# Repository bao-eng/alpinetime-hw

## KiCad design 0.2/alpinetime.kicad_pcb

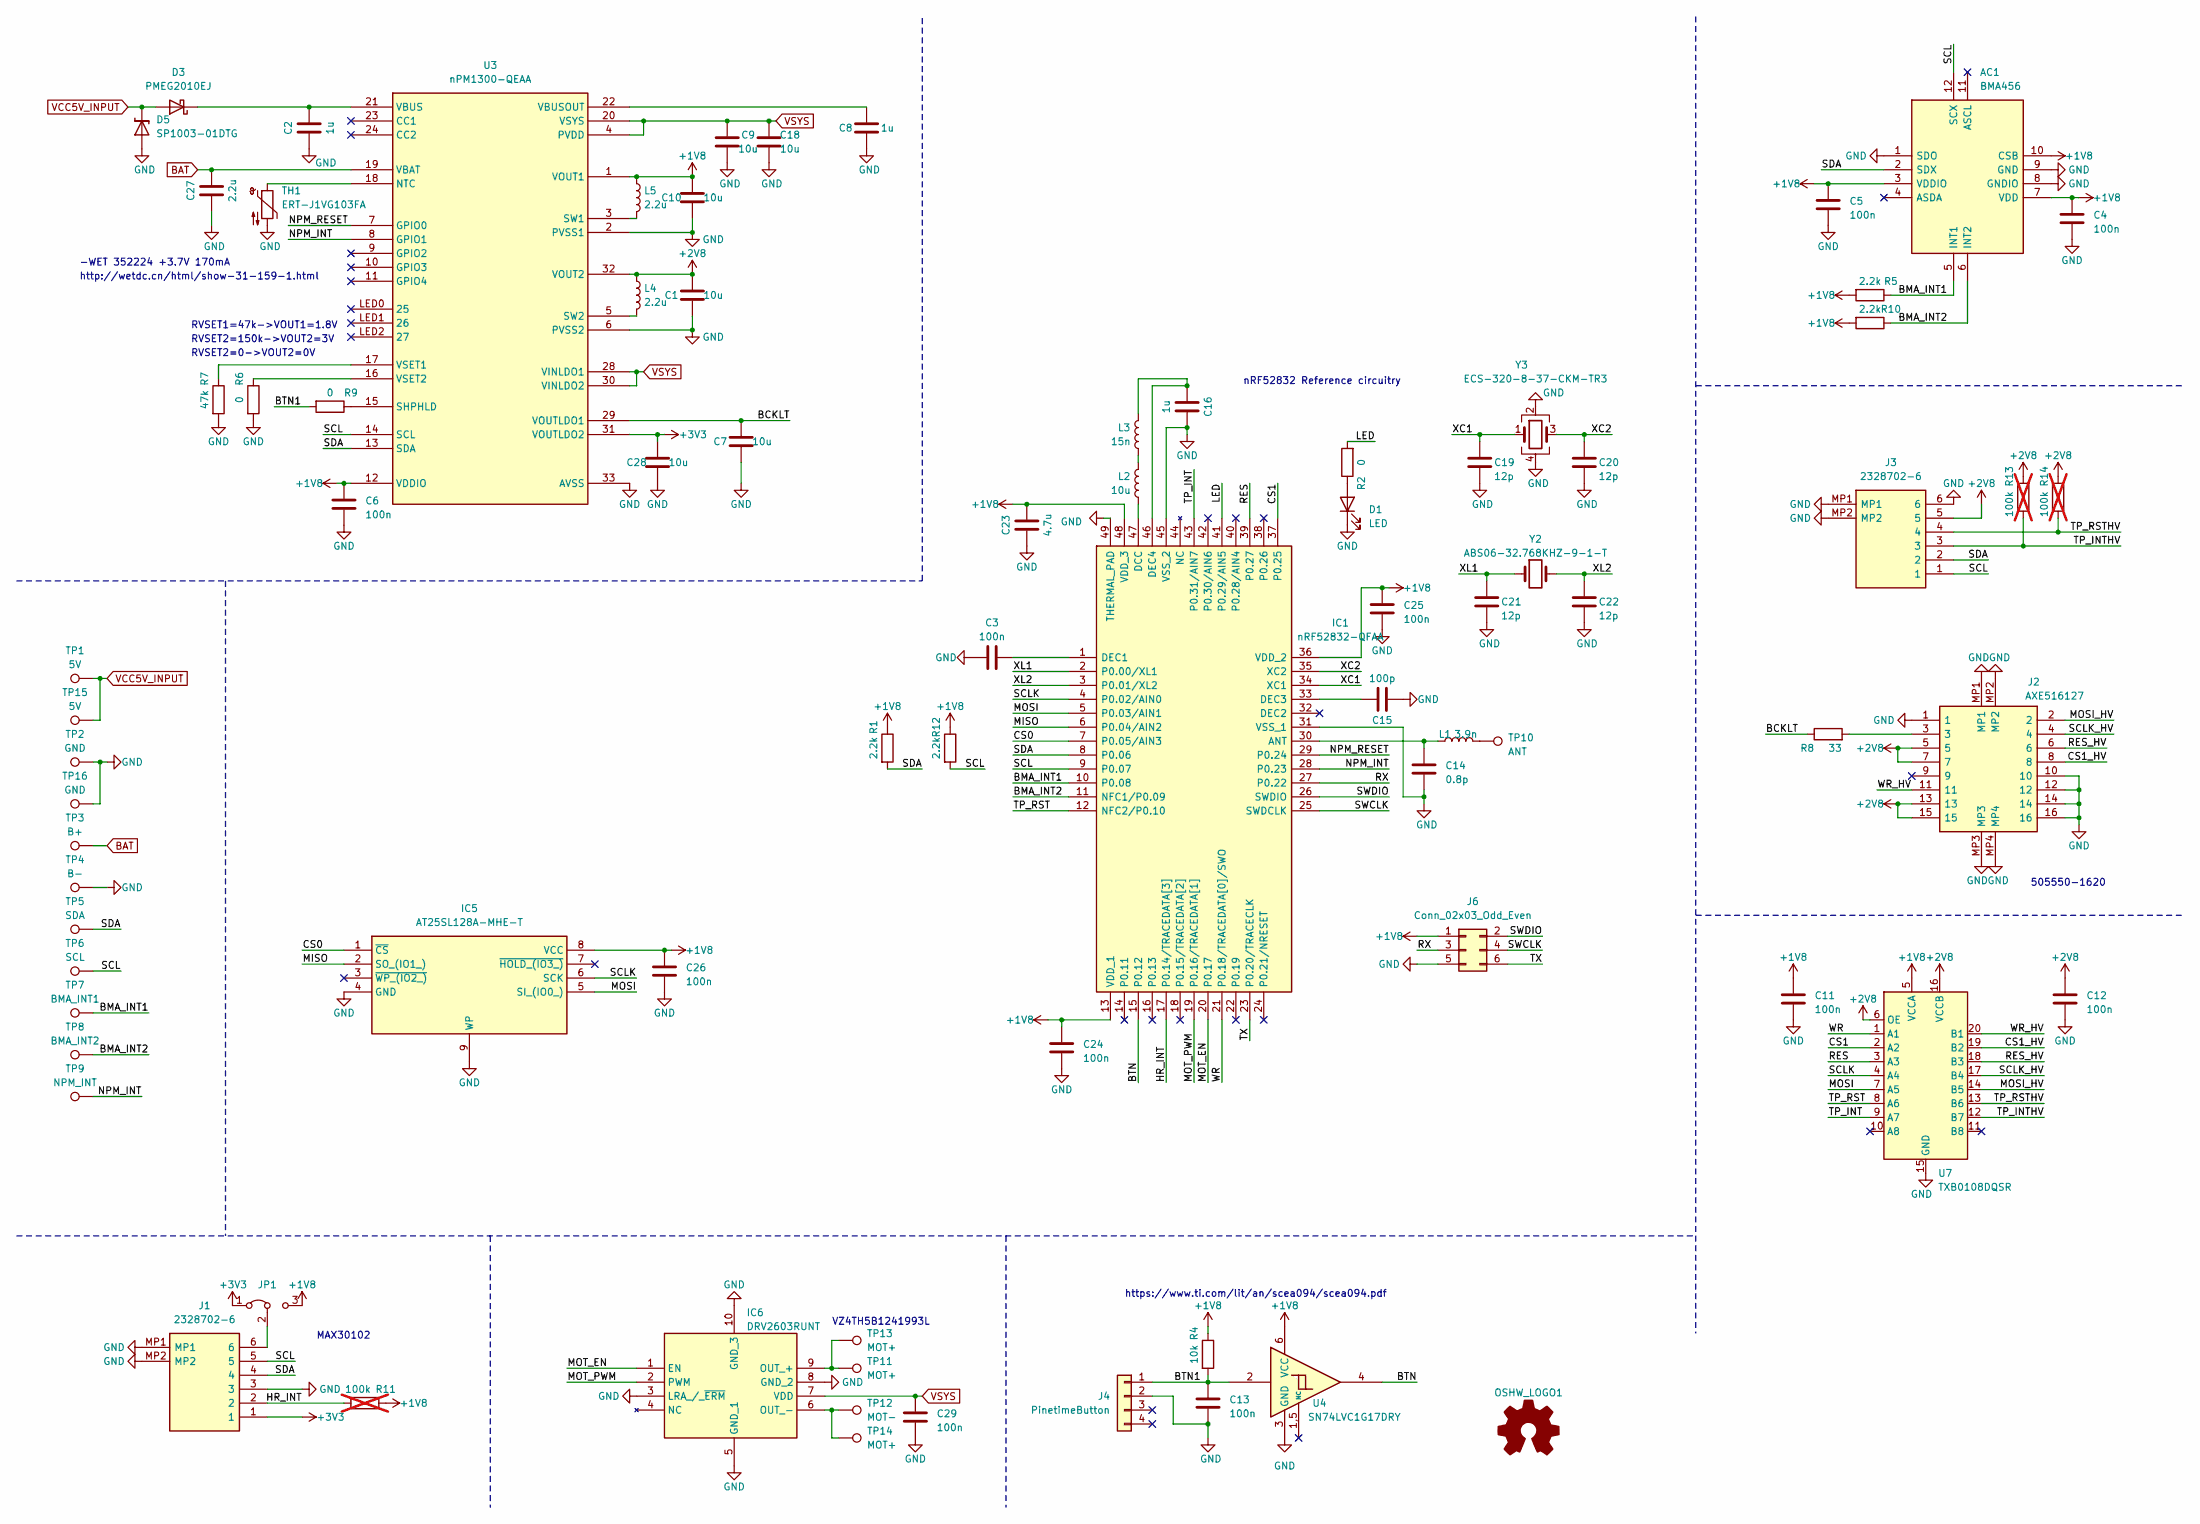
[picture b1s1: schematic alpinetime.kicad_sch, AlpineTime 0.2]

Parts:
AC1: BMA456; BOSCH_LGA-12; Mouser Part Number 262-BMA456
C1, C7, C9, C10, C18, C28: 10u; C_0603_1608Metric; MPN CL10A106KP8NNNC
C2, C8: 1u; C_0603_1608Metric
C3, C4, C5, C6, C11, C12, C13, C24, C25, C26, C29: 100n; C_0402_1005Metric; MPN GCM155R71C104KA55D
C14: 0.8p; C_0402_1005Metric; MPN GJM1555C1HR80WB01D
C15: 100p; C_0402_1005Metric; MPN GRM1555C1H101JA01D
C16: 1u; C_0603_1608Metric; MPN CL10B105KP8NNNC
C19, C20, C21, C22: 12p; C_0402_1005Metric; MPN GRM1555C1H120GA01D
C23: 4.7u; C_0603_1608Metric; MPN CL10A475KQ8NNNC
C27: 2.2u; C_0603_1608Metric; MPN CL10B105KP8NNNC
D1: LED; LED_0402_1005Metric; MPN APHHS1005LSECK/J3-PF
D3: PMEG2010EJ; SODFL2512X80N
D5: SP1003-01DTG; SODFL1406X65N
IC1: nRF52832-QFAA; QFN-48-1EP_6x6mm_P0.4mm_EP4.66x4.66mm; Mouser Part Number 949-NRF52832-QFAA-R7
IC5: AT25SL128A-MHE-T; SON127P600X500X60-9N-D; Mouser Part Number 988-AT25SL128A-MHE-T
IC6: DRV2603RUNT; QFN50P200X200X80-10N-D; Mouser Part Number 595-DRV2603RUNT
J1, J3: 2328702-6; 23287026; Mouser Part Number 571-2328702-6
J2: AXE516127; Mouser Part Number 679-AXE516127
J4: PinetimeButton
J6: Conn_02x03_Odd_Even; PinHeader_2x03_P1.27mm_Vertical
JP1: R_0402_1005Metric_jumper
L1: 3.9n; L_0402_1005Metric; MPN MCL1005-3R9-R
L2: 10u; L_0603_1608Metric; MPN MLZ1608M100WT000
L3: 15n; L_0402_1005Metric; MPN LQG15HS15NJ02D
L4, L5: 2.2u; CIGT201610; MPN CIGT201610EH2R2MNE
OSHW_LOGO1: Logo_Open_Hardware_Small; OSHW_logo.kicad_mod_silkscreen-front_5mm
R1, R5, R10, R12: 2.2k; R_0402_1005Metric; MPN RT0402FRE072K2L
R2: 0; R_0402_1005Metric; MPN RC0402FR-07330RL
R4: 10k; R_0402_1005Metric; MPN RT0402FRE0710KL
R6, R9: 0; R_0402_1005Metric; MPN RT0402FRE072K2L
R7: 47k; R_0402_1005Metric; MPN RT0402FRE072K2L
R8: 33; R_0402_1005Metric; MPN RT0402FRE0733RL
R11, R13, R14: 100k; R_0402_1005Metric; MPN RT0402FRE07100KL; not fitted
TH1: ERT-J1VG103FA; R_0603_1608Metric
TP1: 5V; TestPoint_Pad_D2.0mm
TP2: GND; TestPoint_Pad_D2.0mm
TP3: B+; TestPoint_Pad_Oval_1.0x2.0mm
TP4: B-; TestPoint_Pad_Oval_1.0x2.0mm
TP5: SDA; TestPoint_Pad_D1.0mm
TP6: SCL; TestPoint_Pad_D1.0mm
TP7: BMA_INT1; TestPoint_Pad_D1.0mm
TP8: BMA_INT2; TestPoint_Pad_D1.0mm
TP9: NPM_INT; TestPoint_Pad_D1.0mm
TP10: ANT; TestPoint_Pad_D1.5mm
TP11: MOT+; Pad_7.0x2.5mm
TP12: MOT-; Pad_7.0x2.5mm
TP13, TP14: MOT+; TestPoint_Pad_D1.0mm
TP15: 5V; TestPoint_Pad_D1.0mm
TP16: GND; TestPoint_Pad_D1.0mm
U3: nPM1300-QEAA; QFN-32-1EP_5x5mm_P0.5mm_EP3.3x3.3mm
U4: SN74LVC1G17DRY; SON50P100X145X60-6N
U7: TXB0108DQSR; USON-20_2x4mm_P0.4mm
Y2: ABS06-32.768KHZ-9-1-T; ABS0612732768KHZT
Y3: ECS-320-8-37-CKM-TR3; ECS320837CKMTR3

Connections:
+1V8: AC1.3 (VDDIO), AC1.7 (VDD), AC1.10 (CSB), C4.1, C5.1, C6.1, C10.2, C11.1, C23.2, C24.2, C25.2, C26.1, IC1.13 (VDD_1), IC1.36 (VDD_2), IC1.48 (VDD_3), IC5.8 (VCC), J6.1, JP1.3 (B), L5.1, R1.1, R4.1, R5.2, R10.2, R11.1, R12.1, U3.1 (VOUT1), U3.12 (VDDIO), U4.6 (VCC), U7.5 (VCCA)
+2V8: C1.2, C12.1, J2.5, J2.7, J2.13, J2.15, J3.5, L4.1, R13.1, R14.1, U3.32 (VOUT2), U7.6 (OE), U7.16 (VCCB)
+3V3: C28.2, J1.1, JP1.1 (A), U3.31 (VOUTLDO2)
/BCKLT: C7.2, R8.1, U3.29 (VOUTLDO1)
/BMA_INT1: AC1.5 (INT1), IC1.10 (P0.08), R5.1, TP7.1
/BMA_INT2: AC1.6 (INT2), IC1.11 (NFC1/P0.09), R10.1, TP8.1
/BTN: IC1.15 (P0.12), U4.4
/BTN1: C13.1, J4.1, R4.2, R9.2, U4.2
/CS0: IC1.7 (P0.05/AIN3), IC5.1 (~CS)
/CS1: IC1.37 (P0.25), U7.2 (A2)
/CS1_HV: J2.8, U7.19 (B2)
/HR_INT: IC1.17 (P0.14/TRACEDATA[3]), J1.2, R11.2
/LED: IC1.41 (P0.29/AIN5), R2.2
/MISO: IC1.6 (P0.04/AIN2), IC5.2 (SO_(IO1_))
/MOSI: IC1.5 (P0.03/AIN1), IC5.5 (SI_(IO0_)), U7.7 (A5)
/MOSI_HV: J2.2, U7.14 (B5)
/MOT_EN: IC1.20 (P0.17), IC6.1 (EN)
/MOT_PWM: IC1.19 (P0.16/TRACEDATA[1]), IC6.2 (PWM)
/NPM_INT: IC1.28 (P0.23), TP9.1, U3.8 (GPIO1)
/NPM_RESET: IC1.29 (P0.24), U3.7 (GPIO0)
/RES: IC1.39 (P0.27), U7.3 (A3)
/RES_HV: J2.6, U7.18 (B3)
/RX: IC1.27 (P0.22), J6.3
/SCL: AC1.12 (SCX), IC1.9 (P0.07), J1.5, J3.1, R12.2, TP6.1, U3.14 (SCL)
/SCLK: IC1.4 (P0.02/AIN0), IC5.6 (SCK), U7.4 (A4)
/SCLK_HV: J2.4, U7.17 (B4)
/SDA: AC1.2 (SDX), IC1.8 (P0.06), J1.4, J3.2, R1.2, TP5.1, U3.13 (SDA)
/SWCLK: IC1.25 (SWDCLK), J6.4
/SWDIO: IC1.26 (SWDIO), J6.2
/TP_INT: IC1.43 (P0.31/AIN7), U7.9 (A7)
/TP_INTHV: J3.3, R13.2, U7.12 (B7)
/TP_RST: IC1.12 (NFC2/P0.10), U7.8 (A6)
/TP_RSTHV: J3.4, R14.2, U7.13 (B6)
/TX: IC1.23 (P0.20/TRACECLK), J6.6
/WR: IC1.21 (P0.18/TRACEDATA[0]/SWO), U7.1 (A1)
/WR_HV: J2.11, U7.20 (B1)
/XC1: C19.2, IC1.34 (XC1), Y3.1
/XC2: C20.2, IC1.35 (XC2), Y3.3
/XL1: C21.2, IC1.2 (P0.00/XL1), Y2.1
/XL2: C22.2, IC1.3 (P0.01/XL2), Y2.2
BAT: C27.2, TP3.1, U3.19 (VBAT)
GND: AC1.1 (SDO), AC1.8 (GNDIO), AC1.9 (GND), C1.1, C2.1, C3.1, C4.2, C5.2, C6.2, C7.1, C8.1, C9.1, C10.1, C11.2, C12.2, C13.2, C14.1, C15.1, C16.2, C18.1, C19.1, C20.1, C21.1, C22.1, C23.1, C24.1, C25.1, C26.2, C27.1, C28.1, C29.2, D1.1 (K), D5.2 (A), IC1.31 (VSS_1), IC1.45 (VSS_2), IC1.49 (THERMAL_PAD), IC5.4 (GND), IC5.9 (WP), IC6.3 (LRA_/_~ERM), IC6.5 (GND_1), IC6.8 (GND_2), IC6.10 (GND_3), J1.3, J1.MP1, J1.MP2, J2.1, J2.10, J2.12, J2.14, J2.16, J2.MP1, J2.MP2, J2.MP3, J2.MP4, J3.6, J3.MP1, J3.MP2, J4.2, J6.5, R6.2, R7.2, TH1.2, TP2.1, TP4.1, TP16.1, U3.2 (PVSS1), U3.6 (PVSS2), U3.33 (AVSS), U4.3 (GND), U7.15 (GND), Y3.2, Y3.4
unnamed: D1.2 (A), R2.1
unnamed: C2.2, D3.1 (K), U3.21 (VBUS)
unnamed: C14.2, IC1.30 (ANT), L1.1
unnamed: IC1.47 (DCC), L2.1
unnamed: C3.2, IC1.1 (DEC1)
unnamed: C15.2, IC1.33 (DEC3)
unnamed: C16.1, IC1.46 (DEC4), L3.2
unnamed: IC6.9 (OUT_+), TP11.1, TP13.1
unnamed: IC6.6 (OUT_-), TP12.1, TP14.1
unnamed: J2.3, R8.2
unnamed: J1.6, JP1.2 (C)
unnamed: L1.2, TP10.1
unnamed: L2.2, L3.1
unnamed: TH1.1, U3.18 (NTC)
unnamed: R9.1, U3.15 (SHPHLD)
unnamed: L5.2, U3.3 (SW1)
unnamed: L4.2, U3.5 (SW2)
unnamed: C8.2, U3.22 (VBUSOUT)
unnamed: R7.1, U3.17 (VSET1)
unnamed: R6.1, U3.16 (VSET2)
VCC5V_INPUT: D3.2 (A), D5.1 (K), TP1.1, TP15.1
VSYS: C9.2, C18.2, C29.1, IC6.7 (VDD), U3.4 (PVDD), U3.20 (VSYS), U3.28 (VINLDO1), U3.30 (VINLDO2)

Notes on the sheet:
https://www.ti.com/lit/an/scea094/scea094.pdf
VZ4TH5B1241993L
RVSET2=150k->VOUT2=3V
RVSET1=47k->VOUT1=1.8V
nRF52832 Reference circuitry
http://wetdc.cn/html/show-31-159-1.html
-WET 352224 +3.7V 170mA
505550-1620
MAX30102
RVSET2=0->VOUT2=0V

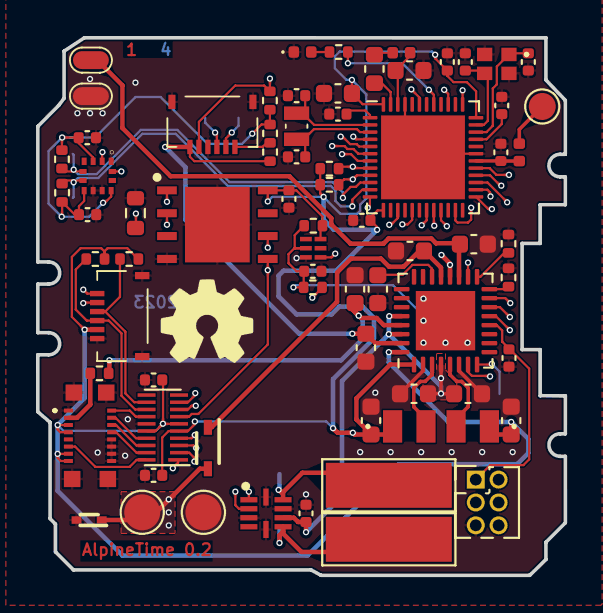
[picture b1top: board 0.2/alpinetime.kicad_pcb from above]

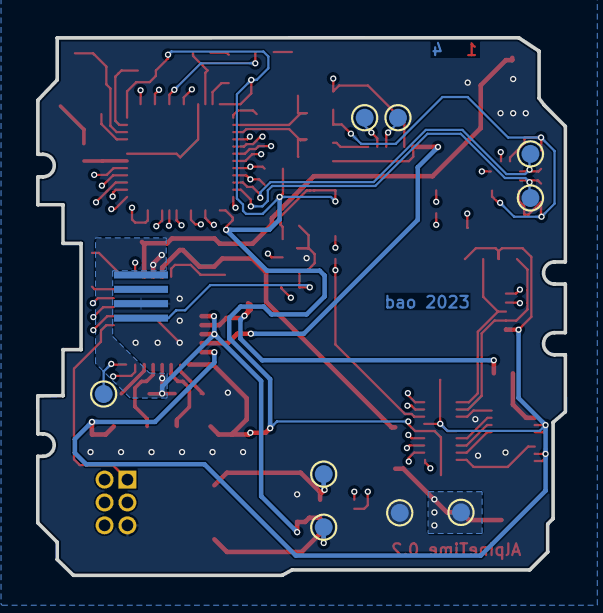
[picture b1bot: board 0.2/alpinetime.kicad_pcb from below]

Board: 4 copper layers, 29.3 x 29.9 mm, 82 parts (10 on the bottom side), 64 nets.

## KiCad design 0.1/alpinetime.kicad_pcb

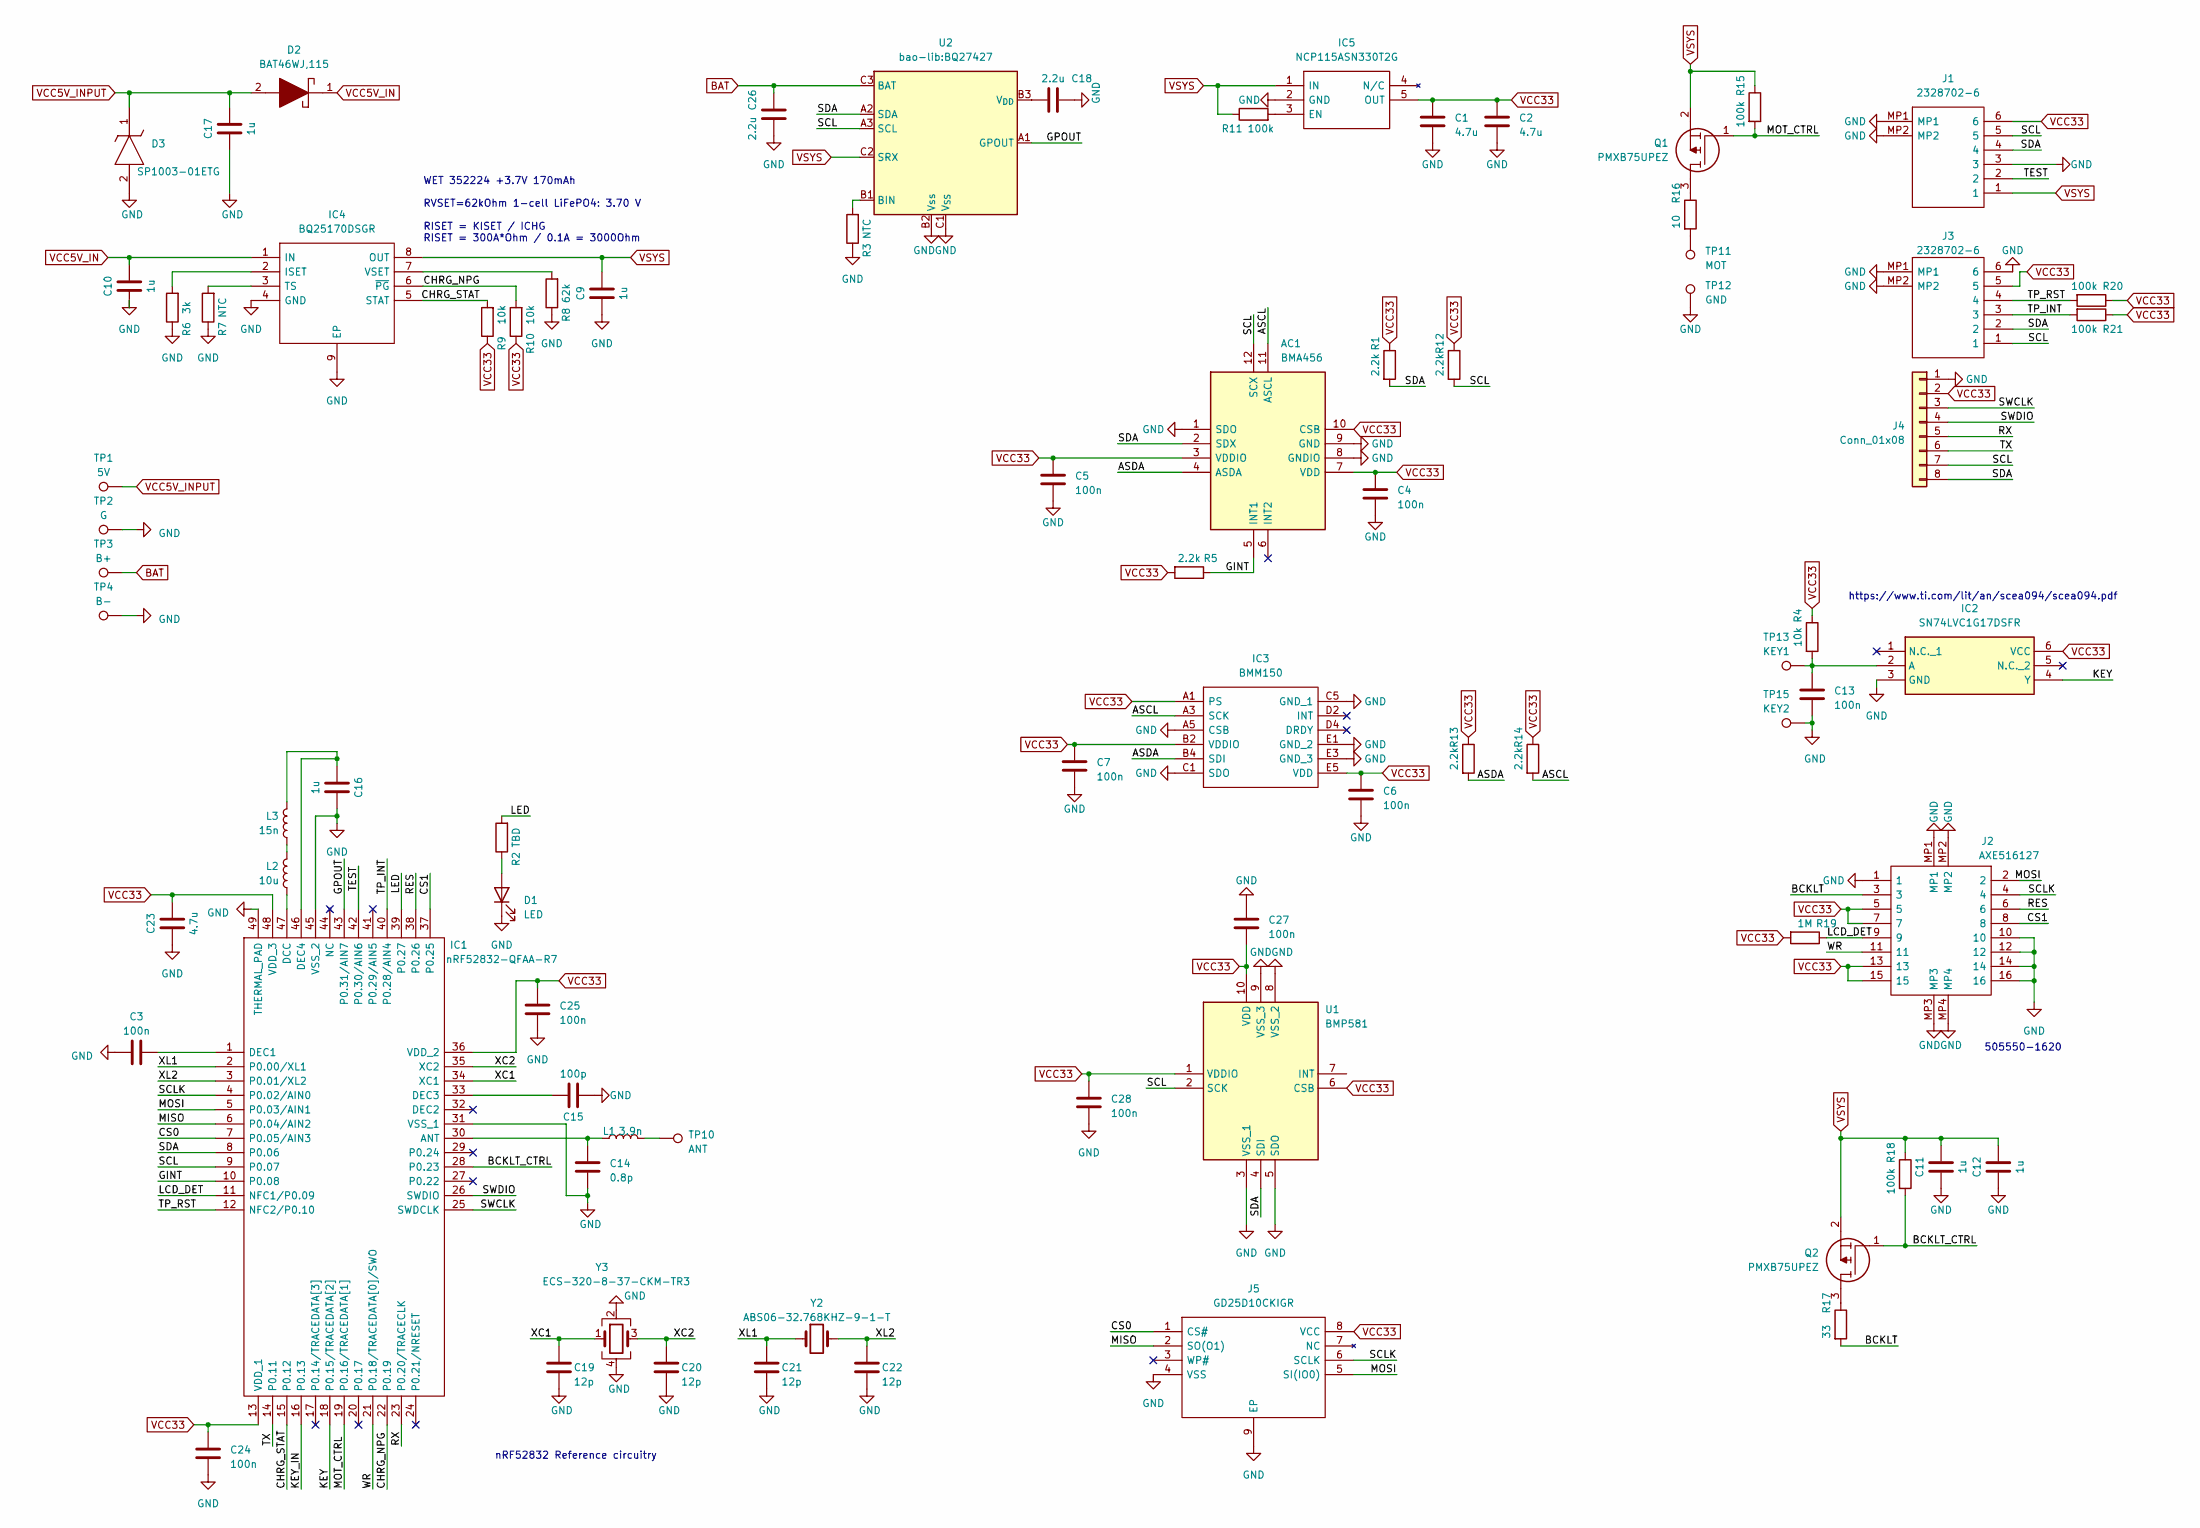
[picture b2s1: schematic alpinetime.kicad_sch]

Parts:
AC1: BMA456; BOSCH_LGA-12; Mouser Part Number 262-BMA456
C1, C2: 4.7u; C_0603_1608Metric; MPN CL10A475KP8NNNC
C3, C4, C5, C6, C7, C13, C24, C25, C27, C28: 100n; C_0402_1005Metric; MPN GCM155R71C104KA55D
C9, C10, C11, C12, C16, C17: 1u; C_0603_1608Metric; MPN CL10B105KP8NNNC
C14: 0.8p; C_0402_1005Metric; MPN GJM1555C1HR80WB01D
C15: 100p; C_0402_1005Metric; MPN GRM1555C1H101JA01D
C18, C26: 2.2u; C_0603_1608Metric; MPN CL10B225KP8NNNC
C19, C20, C21, C22: 12p; C_0402_1005Metric; MPN GRM1555C1H120GA01D
C23: 4.7u; C_0603_1608Metric
D1: LED; LED_0402_1005Metric; MPN LT QH9G-Q2OO-25-2Z4Y
D2: BAT46WJ,115; SODFL2512X80N; Mouser Part Number 771-BAT46WJ115
D3: SP1003-01ETG; SOD882; Mouser Part Number 576-SP1003-01ETG
IC1: nRF52832-QFAA-R7; QFN40P600X600X90-49N-D; Mouser Part Number 949-NRF52832-QFAA-R7
IC2: SN74LVC1G17DSFR; SON35P100X100X40-6N; Mouser Part Number 595-SN74LVC1G17DSFR
IC3: BMM150; Mouser Part Number 262-BMM150
IC4: BQ25170DSGR; SON50P200X200X80-9N; Mouser Part Number 595-BQ25170DSGR
IC5: NCP115ASN330T2G; SOT95P275X110-5N; Mouser Part Number 863-NCP115ASN330T2G
J1, J3: 2328702-6; 23287026; Mouser Part Number 571-2328702-6
J2: AXE516127; Mouser Part Number 679-AXE516127
J4: Conn_01x08; PinSocket_1x08_P1.27mm_Vertical
J5: GD25D10CKIGR; SON40P150X150X50-9N; Mouser Part Number 363-GD25D10CKIGR
L1: 3.9n; L_0402_1005Metric; MPN MCL1005-3R9-R
L2: 10u; L_0603_1608Metric; MPN MLZ1608M100WT000
L3: 15n; L_0402_1005Metric; MPN LQG15HS15NJ02D
Q1, Q2: PMXB75UPEZ; Mouser Part Number 771-PMXB75UPEZ
R1, R5, R12, R13, R14: 2.2k; R_0402_1005Metric; MPN RT0402FRE072K2L
R2: TBD; R_0402_1005Metric
R3, R7: NTC; R_0402_1005Metric; MPN 103KT1005T-1P
R4, R9, R10: 10k; R_0402_1005Metric; MPN RT0402FRE0710KL
R6: 3k; R_0402_1005Metric; MPN ERA-2AEB302X
R8: 62k; R_0402_1005Metric; MPN RT0402BRD0762KL
R11, R15, R18, R20, R21: 100k; R_0402_1005Metric; MPN RT0402FRE07100KL
R16: 10; R_0402_1005Metric; MPN RT0402FRE0710RL
R17: 33; R_0402_1005Metric; MPN RT0402FRE0733RL
R19: 1M; R_0402_1005Metric; MPN RC0402FR-131ML
TP1: 5V; TestPoint_Pad_D2.0mm
TP2: G; TestPoint_Pad_D2.0mm
TP3: B+; TestPoint_Pad_D1.5mm
TP4: B-; TestPoint_Pad_D1.5mm
TP10: ANT; TestPoint_Pad_D1.5mm
TP11: MOT; TestPoint_Pad_2.0x2.0mm
TP12: GND; TestPoint_Pad_2.0x2.0mm
TP13: KEY1; TestPoint_Pad_2.0x2.0mm
TP15: KEY2; TestPoint_Pad_2.0x2.0mm
U1: BMP581; Mouser Part Number 262-BMP581
U2: bao-lib:BQ27427; Texas_DSBGA-9_1.4715x1.4715mm_Layout3x3_P0.5mm
Y2: ABS06-32.768KHZ-9-1-T; ABS0612732768KHZT
Y3: ECS-320-8-37-CKM-TR3; ECS320837CKMTR3

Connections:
/ASCL: AC1.11 (ASCL), IC3.A3 (SCK), R14.2
/ASDA: AC1.4 (ASDA), IC3.B4 (SDI), R13.2
/BCKLT: J2.3, R17.2
/BCKLT_CTRL: IC1.28 (P0.23), Q2.1, R18.2
/CHRG_NPG: IC1.22 (P0.19), IC4.6 (~PG), R10.2
/CHRG_STAT: IC1.15 (P0.12), IC4.5 (STAT), R9.2
/CS0: IC1.7 (P0.05/AIN3), J5.1 (CS#)
/CS1: IC1.37 (P0.25), J2.8
/GINT: AC1.5 (INT1), IC1.10 (P0.08), R5.1
/GPOUT: IC1.43 (P0.31/AIN7), U2.A1 (GPOUT)
/KEY: IC1.18 (P0.15/TRACEDATA[2]), IC2.4 (Y)
/KEY_IN: IC1.16 (P0.13)
/LCD_DET: IC1.11 (NFC1/P0.09), J2.9, R19.1
/LED: IC1.39 (P0.27), R2.2
/MISO: IC1.6 (P0.04/AIN2), J5.2 (SO(O1))
/MOSI: IC1.5 (P0.03/AIN1), J2.2, J5.5 (SI(IO0))
/MOT_CTRL: IC1.19 (P0.16/TRACEDATA[1]), Q1.1, R15.2
/RES: IC1.38 (P0.26), J2.6
/RX: IC1.23 (P0.20/TRACECLK), J4.5
/SCL: AC1.12 (SCX), IC1.9 (P0.07), J1.5, J3.1, J4.7, R12.2, U1.2 (SCK), U2.A3 (SCL)
/SCLK: IC1.4 (P0.02/AIN0), J2.4, J5.6 (SCLK)
/SDA: AC1.2 (SDX), IC1.8 (P0.06), J1.4, J3.2, J4.8, R1.2, U1.4 (SDI), U2.A2 (SDA)
/SWCLK: IC1.25 (SWDCLK), J4.3
/SWDIO: IC1.26 (SWDIO), J4.4
/TEST: IC1.42 (P0.30/AIN6), J1.2
/TP_INT: IC1.40 (P0.28/AIN4), J3.3, R21.2
/TP_RST: IC1.12 (NFC2/P0.10), J3.4, R20.2
/TX: IC1.14 (P0.11), J4.6
/WR: IC1.21 (P0.18/TRACEDATA[0]/SWO), J2.11
/XC1: C19.2, IC1.34 (XC1), Y3.1
/XC2: C20.2, IC1.35 (XC2), Y3.3
/XL1: C21.2, IC1.2 (P0.00/XL1), Y2.1
/XL2: C22.2, IC1.3 (P0.01/XL2), Y2.2
BAT: C26.1, TP3.1, U2.C3 (BAT)
GND: AC1.1 (SDO), AC1.8 (GNDIO), AC1.9 (GND), C1.2, C2.2, C3.1, C4.2, C5.2, C6.2, C7.2, C9.1, C10.1, C11.1, C12.1, C13.2, C14.1, C15.1, C16.2, C17.1, C18.1, C19.1, C20.1, C21.1, C22.1, C23.1, C24.1, C25.1, C26.2, C27.1, C28.2, D1.1 (K), D3.2, IC1.31 (VSS_1), IC1.45 (VSS_2), IC1.49 (THERMAL_PAD), IC2.3 (GND), IC3.A5 (CSB), IC3.C1 (SDO), IC3.C5 (GND_1), IC3.E1 (GND_2), IC3.E3 (GND_3), IC4.4 (GND), IC4.9 (EP), IC5.2 (GND), J1.3, J1.MP1, J1.MP2, J2.1, J2.10, J2.12, J2.14, J2.16, J2.MP1, J2.MP2, J2.MP3, J2.MP4, J3.6, J3.MP1, J3.MP2, J4.1, J5.4 (VSS), J5.9 (EP), R3.1, R6.1, R7.1, R8.1, TP2.1, TP4.1, TP12.1, TP15.1, U1.3 (VSS_1), U1.5 (SDO), U1.8 (VSS_2), U1.9 (VSS_3), U2.B2 (Vss), U2.C1 (V_{SS}), Y3.2, Y3.4
unnamed: D1.2 (A), R2.1
unnamed: C14.2, IC1.30 (ANT), L1.1
unnamed: IC1.47 (DCC), L2.1
unnamed: C3.2, IC1.1 (DEC1)
unnamed: C15.2, IC1.33 (DEC3)
unnamed: C16.1, IC1.46 (DEC4), L3.2
unnamed: C13.1, IC2.2 (A), R4.2, TP13.1
unnamed: IC4.2 (ISET), R6.2
unnamed: IC4.3 (TS), R7.2
unnamed: IC4.7 (VSET), R8.2
unnamed: IC5.3 (EN), R11.2
unnamed: L1.2, TP10.1
unnamed: L2.2, L3.1
unnamed: Q1.3, R16.1
unnamed: Q2.3, R17.1
unnamed: R16.2, TP11.1
unnamed: R3.2, U2.B1 (BIN)
unnamed: C18.2, U2.B3 (V_{DD})
VCC5V_IN: C10.2, D2.1, IC4.1 (IN)
VCC5V_INPUT: C17.2, D2.2, D3.1, TP1.1
VCC33: AC1.3 (VDDIO), AC1.7 (VDD), AC1.10 (CSB), C1.1, C2.1, C4.1, C5.1, C6.1, C7.1, C23.2, C24.2, C25.2, C27.2, C28.1, IC1.13 (VDD_1), IC1.36 (VDD_2), IC1.48 (VDD_3), IC2.6 (VCC), IC3.A1 (PS), IC3.B2 (VDDIO), IC3.E5 (VDD), IC5.5 (OUT), J1.6, J2.5, J2.7, J2.13, J2.15, J3.5, J4.2, J5.8 (VCC), R1.1, R4.1, R5.2, R9.1, R10.1, R12.1, R13.1, R14.1, R19.2, R20.1, R21.1, U1.1 (VDDIO), U1.6 (CSB), U1.10 (VDD)
VSYS: C9.2, C11.2, C12.2, IC4.8 (OUT), IC5.1 (IN), J1.1, Q1.2, Q2.2, R11.1, R15.1, R18.1, U2.C2 (SRX)

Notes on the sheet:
https://www.ti.com/lit/an/scea094/scea094.pdf
RVSET=62kOhm 1-cell LiFePO4: 3.70 V RISET = KISET / ICHG RISET = 300A*Ohm / 0.1A = 3000Ohm
nRF52832 Reference circuitry
WET 352224 +3.7V 170mAh
505550-1620

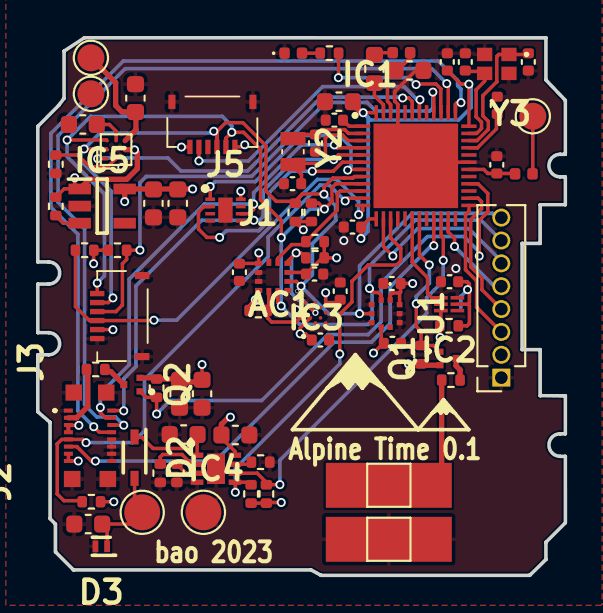
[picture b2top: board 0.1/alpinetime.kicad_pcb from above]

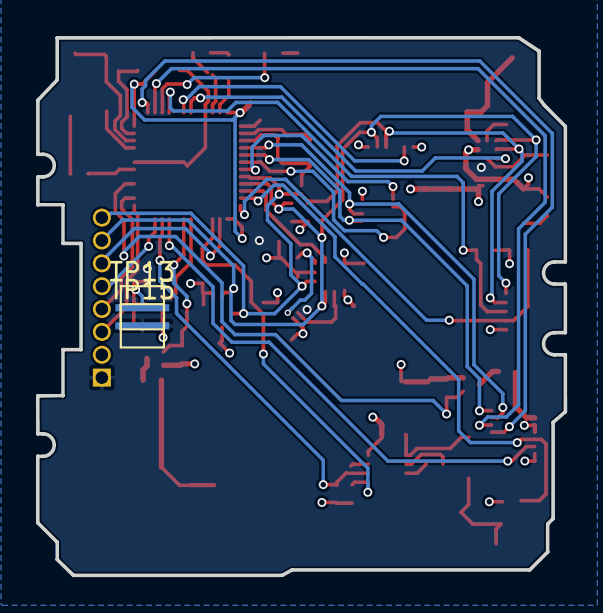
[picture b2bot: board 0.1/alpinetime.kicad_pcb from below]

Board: 4 copper layers, 29.3 x 29.9 mm, 80 parts (2 on the bottom side), 56 nets.

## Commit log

2023-11-14 kicad library subproject added
2023-11-14 alpinetime 0.1 uploaded
2023-11-14 bao-lib updated
2023-11-15 relative path fixed
2023-11-15 value property fixed
2023-11-15 .gitignore added
2023-11-15 ignore lock files
2023-11-15 lock files ignoring fixed
2023-11-15 ignore fp-info-cache files
2023-11-15 .gitignore updated
2024-12-16 alpinetime 0.2 uploaded
